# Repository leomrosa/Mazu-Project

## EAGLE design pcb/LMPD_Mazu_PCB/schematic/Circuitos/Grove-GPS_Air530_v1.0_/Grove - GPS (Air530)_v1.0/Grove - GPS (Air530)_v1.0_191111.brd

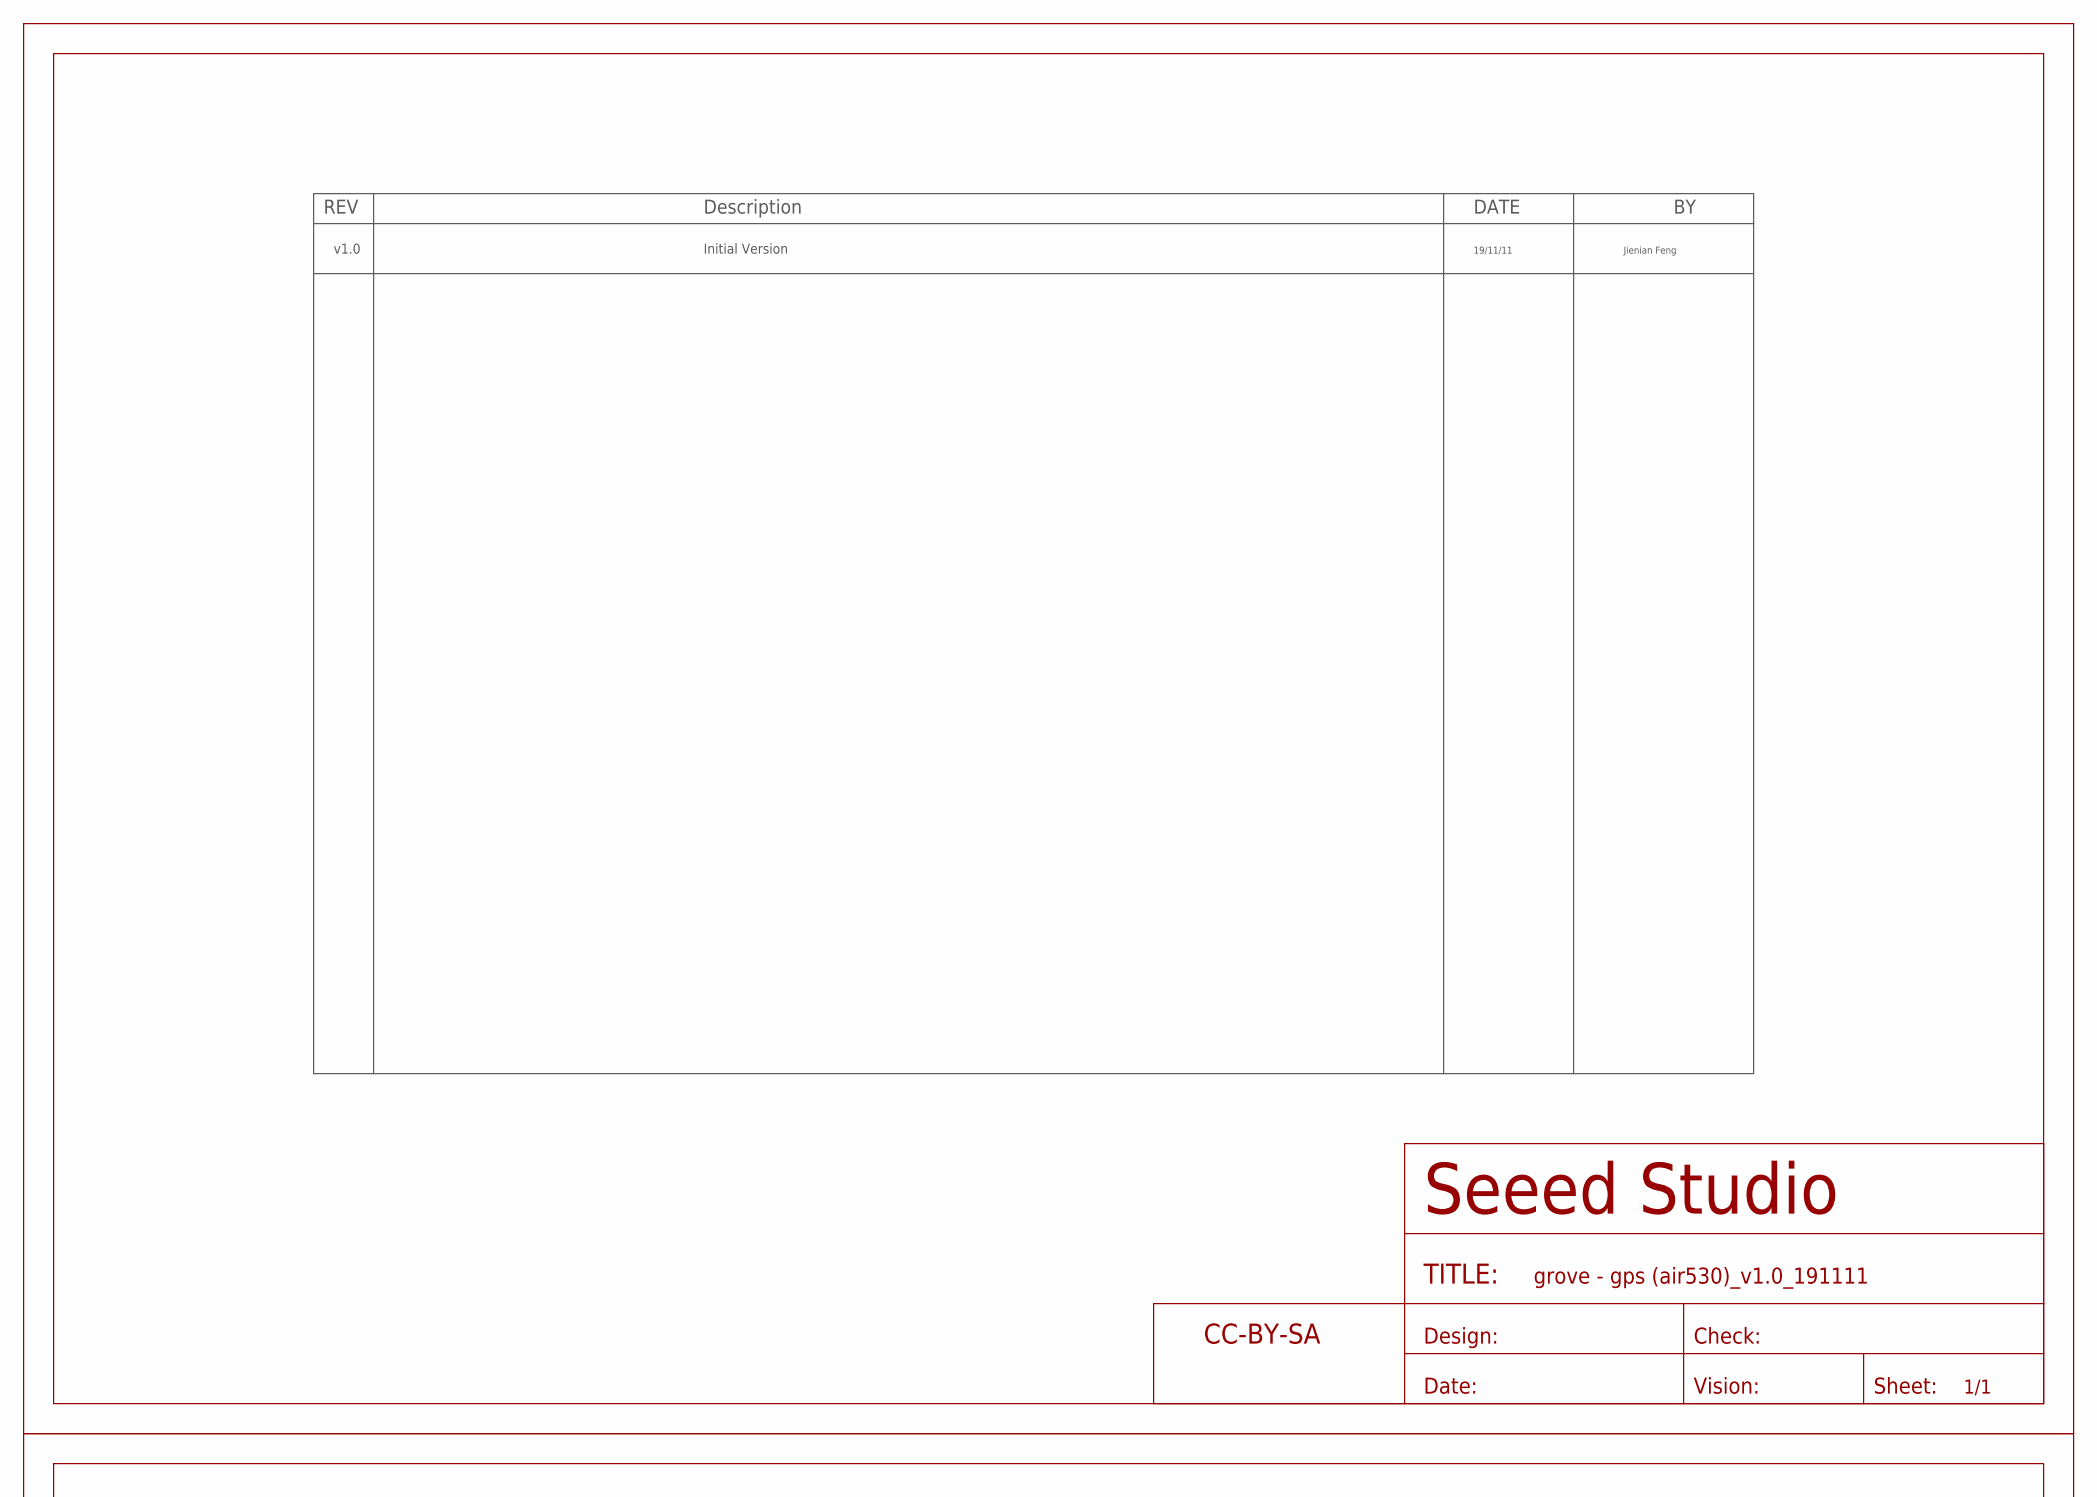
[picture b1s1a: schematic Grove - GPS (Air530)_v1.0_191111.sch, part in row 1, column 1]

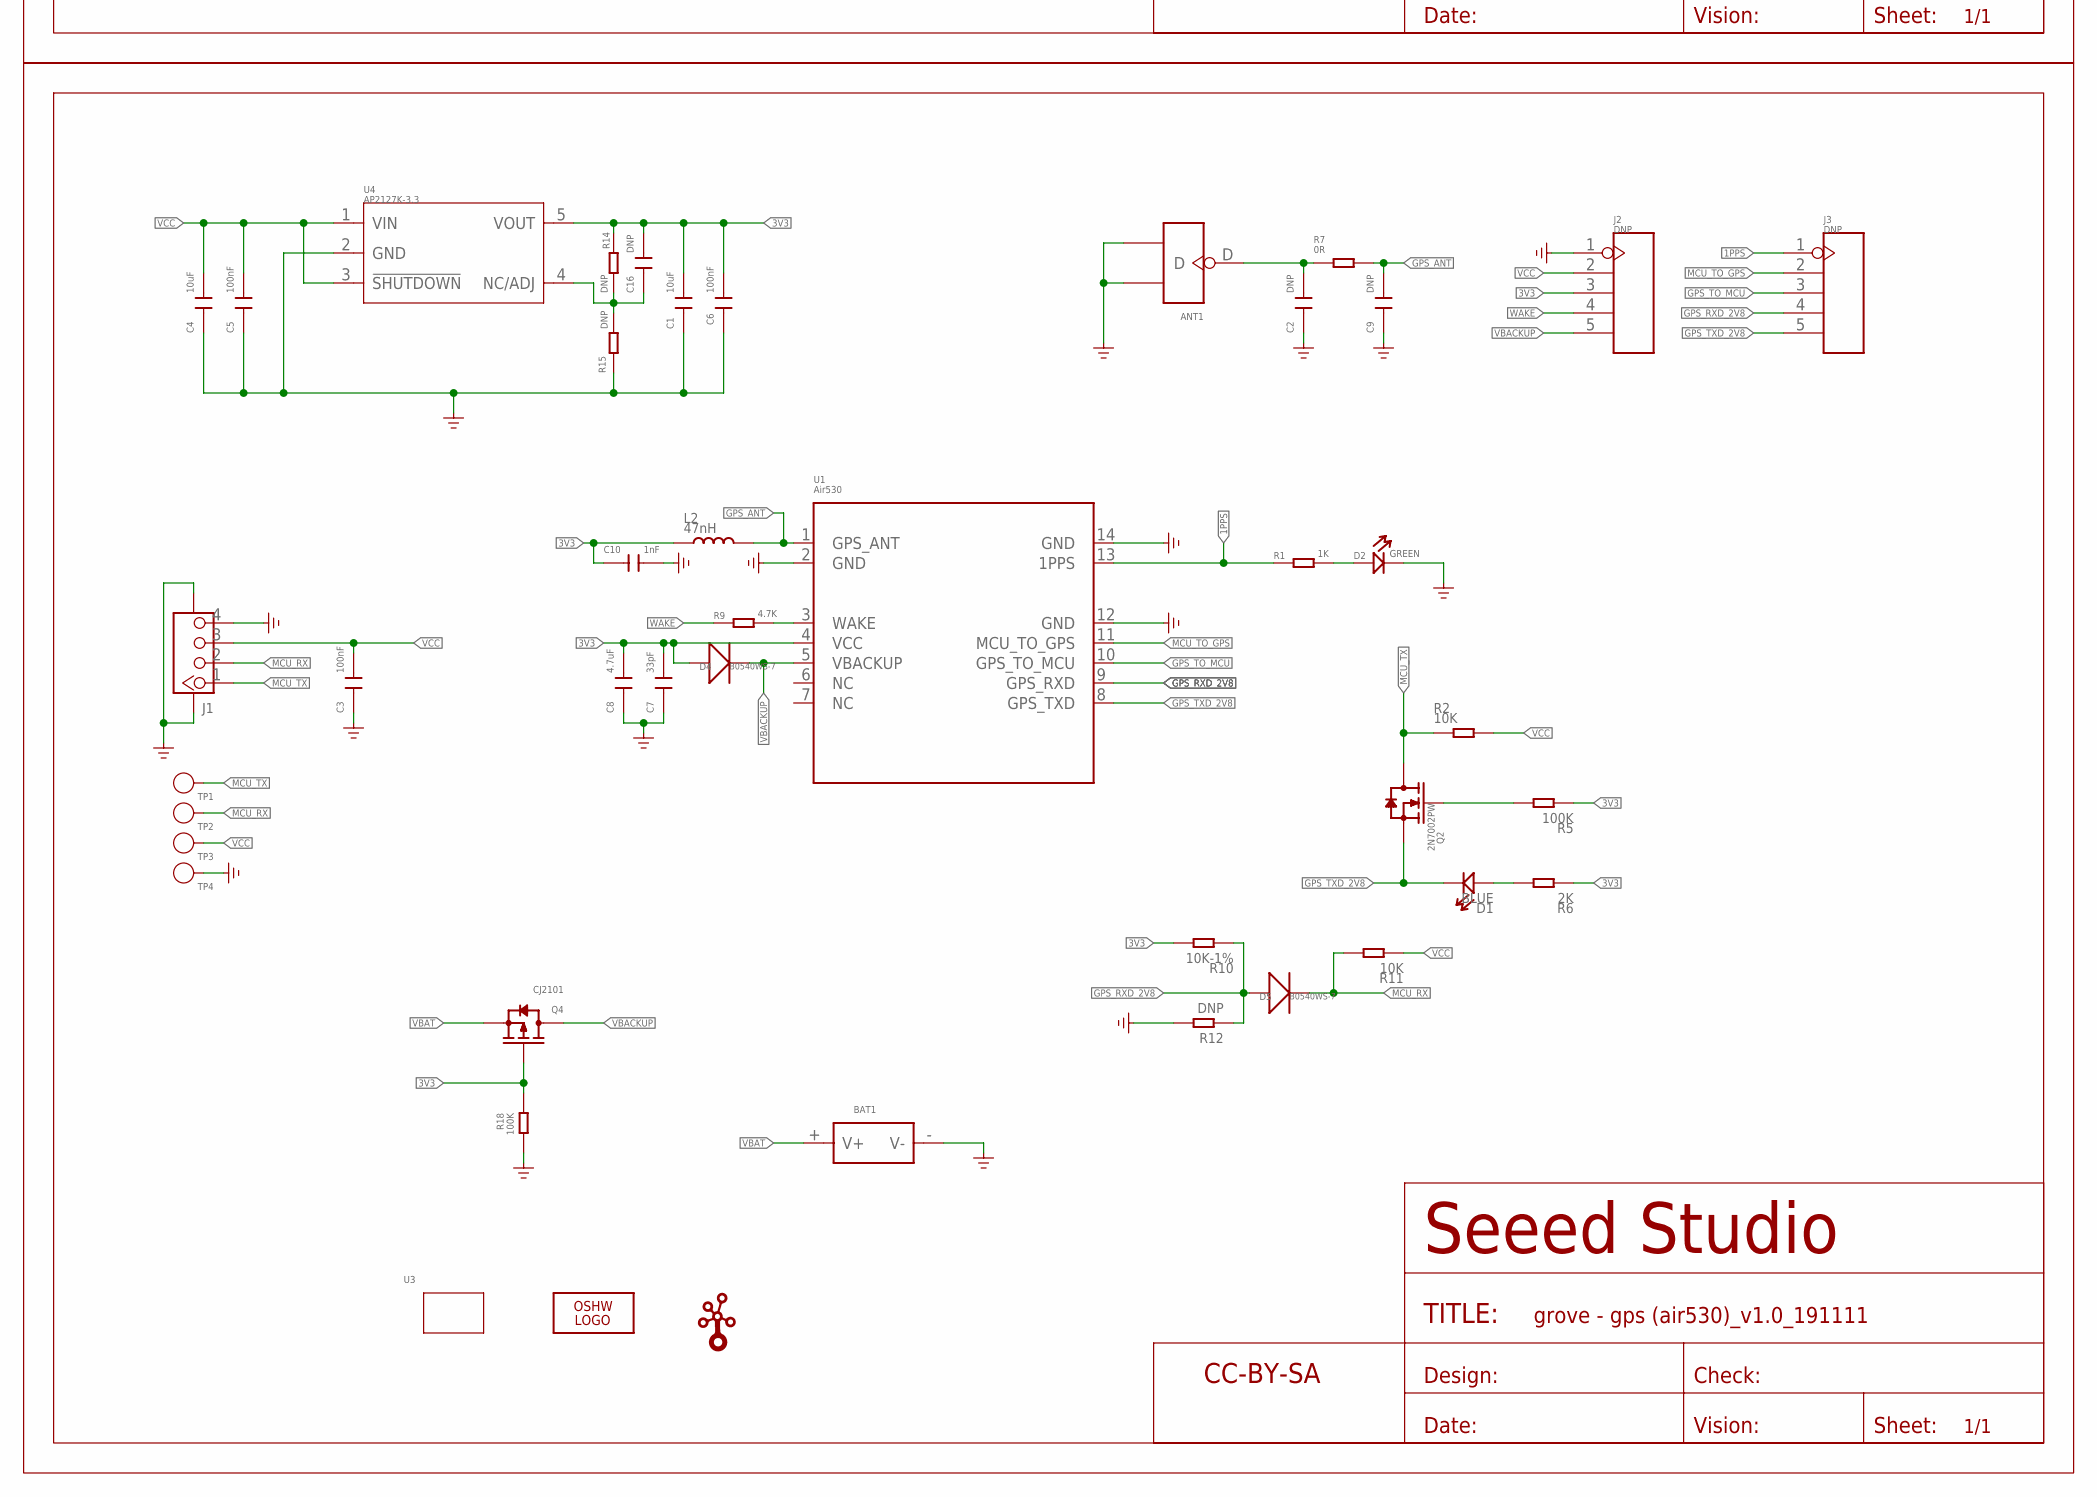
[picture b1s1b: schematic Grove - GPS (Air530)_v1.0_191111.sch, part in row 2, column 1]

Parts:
ANT1: ANTENNA-U-FL-320110048; U-FL3P-SMD-2.6X2.6X1.0MM
BAT1: BAT-HOLDER'SMD-1220'; BAT2P-SMD-16.4-CR1220
C1, C4: 10uF; C0603
C2, C9, C16: DNP; C0402
C3, C5, C6: 100nF; C0402
C7: 33pF; C0402
C8: 4.7uF; C0402
C10: 1nF; C0402
D1: BLUE; LED-0402
D2: GREEN; LED-0402
D4, D5: B0540WS-7; SOD323
FR1, FR2: SEEEDSTUDIO-OPEN-SCH-FRAME; SEEEDSTUDIO-PCB-FRAME
J1: GROVE-CONNECTOR-SMD-320110030; HW4-SMD-2.0
J2, J3: DNP; H5-2.54
L2: 47nH; L0402
LOGO1: LOGO-OSHW-FILLX0200-NT; OSHW_FILLX200_NOTEXT
Q2: 2N7002PW; SOT-323
Q4: CJ2101; SOT-323
R1: 1K; R0402
R2, R11: 10K; R0402
R5, R18: 100K; R0402
R6: 2K; R0402
R7: 0R; R0402
R9: 4.7K; R0402
R10: 10K-1%; R0402
R12, R14, R15: DNP; R0402
TP1, TP2, TP3, TP4: TEST-POINT'4545'; TP-D45MIL
U1: Air530; MOUDLE14-GPS-9.9X12.9MM
U3: GROVE-1X2-TOP; GROVE-1*2-TEST-PLATFORM-TOP
U4: AP2127K-3.3; SOT-23-5
U$1: LOGO-GROVE; GROVE-SILK-BIG

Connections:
1PPS: J3.1, R1.1, U1.13 (1PPS)
3V3: C1.2, C6.2, C7.2, C8.2, C10.1, C16.2, D4.+, J2.3, L2.1, Q4.1 (G), R5.1, R6.1, R10.2, R14.2, R18.1, U1.4 (VCC), U4.5 (VOUT)
GND: ANT1.GND1, ANT1.GND2, BAT1.- (V-), C1.1, C2.1, C3.1, C4.1, C5.1, C6.1, C7.1, C8.1, C9.1, C10.2, D2.-, J1.4, J1.SS1, J1.SS2, J2.1, R12.2, R15.1, R18.2, TP4.T, U1.2 (GND), U1.12 (GND), U1.14 (GND), U4.2 (GND)
GPS_ANT: C9.2, L2.2, R7.2, U1.1 (GPS_ANT)
GPS_RXD_2V8: D5.+, J3.4, R10.1, R12.1, U1.9 (GPS_RXD)
GPS_TO_MCU: J3.3, U1.10 (GPS_TO_MCU)
GPS_TXD_2V8: D1.-, J3.5, Q2.2 (S), U1.8 (GPS_TXD)
MCU_RX: D5.-, J1.2, R11.2, TP2.T
MCU_TO_GPS: J3.2, U1.11 (MCU_TO_GPS)
MCU_TX: J1.1, Q2.3 (D), R2.1, TP1.T
unnamed: D2.+, R1.2
unnamed: ANT1.D, C2.2, R7.1
unnamed: R9.2, U1.3 (WAKE)
unnamed: C16.1, R14.1, R15.2, U4.4 (NC/ADJ)
unnamed: D1.+, R6.2
unnamed: Q2.1 (G), R5.2
VBACKUP: D4.-, J2.5, Q4.3 (D), U1.5 (VBACKUP)
VBAT: BAT1.+ (V+), Q4.2 (S)
VCC: C3.2, C4.2, C5.2, J1.3, J2.2, R2.2, R11.1, TP3.T, U4.1 (VIN), U4.3 (!SHUTDOWN)
WAKE: J2.4, R9.1

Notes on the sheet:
v1.0
Initial Version
19/11/11
Jienian Feng

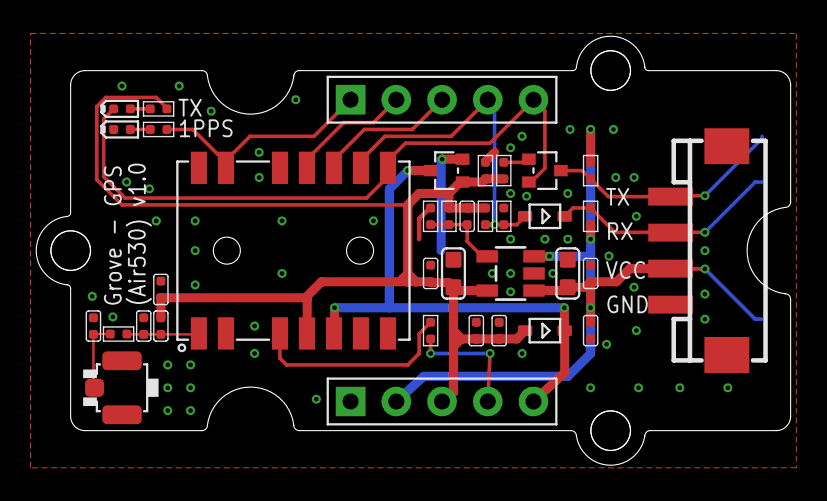
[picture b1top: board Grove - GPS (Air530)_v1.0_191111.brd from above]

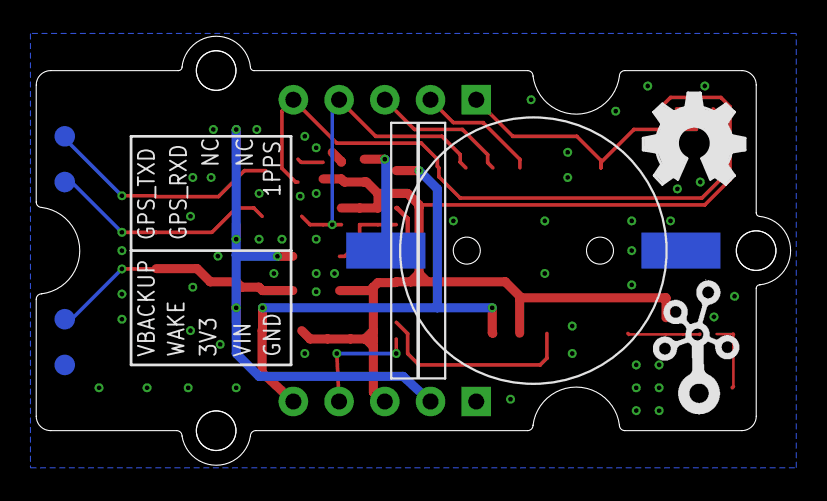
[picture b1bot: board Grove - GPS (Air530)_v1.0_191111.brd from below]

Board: 2 copper layers, 41.9 x 23.8 mm, 46 parts (7 on the bottom side), 20 nets.

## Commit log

2024-10-28 Adicionei codigo ESP
2024-10-28 Adicinei os Results
2024-10-28 Adicioneo«i codigo da app android e ficheiros kicad
2024-10-28 Removi
2024-10-28 Adicionei ficheiros kicad

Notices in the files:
parts and their libraries:
moudle-new: This work is licensed under the Creative Commons Attribution 4.0 International License.
To view a copy of this license,visit:
http://creativecommons.org/licenses/by-sa/4.0
moudle-new: CC-BY-SA
